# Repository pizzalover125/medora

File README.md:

# medora
A smart pill organizer. A project that saves lives.

### Why medora?
Medication nonadherence is the failure to take medication as prescribed, whether by skipping doses, taking the wrong amount, or stopping treatment early.

* Medication nonadherence contributes to roughly 125,000 deaths every year in the U.S. (Kim and Sarah A.)
* Pill organizer users saw adherence rise from 65% to as high as 100% within months (Rathod et al.)
* Patients using a smart pill organizer were 60% more compliant than those without one, nearly double the 32% improvement seen with a standard pillbox (Godin)

In the status quo, there smart pill organizers are expensive costing an average of $150 - $200 with an added monthly subscription on top. For many Americans, this is simply too out-of-reach. Additionally, many of the apps that come with the organizers are outdated and hard to use. I wanted to fix this by creating a low-cost, modern, smart pill organizer. 

### PCB

The PCB was designed in KiCAD.

### CAD

The CAD was designed in Onshape. You can view the link here: https://cad.onshape.com/documents/c1d6b76cfe1063ae9996d35d/w/b74057f0558c55e37de9882a/e/dce7fc6940c214e434cc5424?renderMode=0&uiState=6a616dc37022e90ea2108f99. There are magnets that hold together the lid and the case. 

### BOM 
A detailed bill of materials can be viewed here: https://docs.google.com/spreadsheets/d/15uKd0en9vIonSRlWCDsz52HICyDAk6iSbPfcEML8UvA/edit?usp=sharing.

### Credits
Big thanks to Hack Club for making this project possible!

### Sponsorship

This project's PCBs are sponsored by PCBWay, a leading manufacturer for PCB fabrication, assembly, 3D printing, and more.

#### About PCBWay

PCBWay offers PCB prototyping and manufacturing, PCB assembly, 3D printing, CNC machining, and other on-demand manufacturing services for makers, students, and engineers worldwide.

#### Project Background

This is a smart pill organizer — an 8-compartment device with LED indicators to help users track and remember their medication schedule. Building it required a custom PCB to house the microcontroller, LED drivers, and compartment sensors in a compact enclosure.

#### Order Process

1. **Download the Gerber files** from this repo.
2. **Go to [PCBWay.com](https://www.pcbway.com)** and click **"Instant Quote"** on the homepage.
3. **Upload the Gerber `.zip`** from this repo. PCBWay auto-detects your board dimensions, layer count, and other specs — verify these match: 190mm × 90mm, 2-layer.
4. **Set your order specs:**
   - Quantity (e.g. 5 or 10 boards)
   - Board thickness (1.6mm)
   - Copper weight (1oz standard)
   - Surface finish (HASL or ENIG)
   - Solder mask & silkscreen color
5. **Review the quote** and confirm cost/production time.
6. **Place the order** and confirm shipping address/method.
7. **Track production** — PCBWay provides status updates through fabrication and a tracking number once shipped.

#### Unboxing

Will be updated once I receive the boards!

#### Board Dimensions & Precision

Board size: 190 mm × 90 mm
Board thickness: 1.6 mm (standard)
Copper layers: 2-layer
Minimum trace width: 0.2 mm (KiCad default)
Minimum clearance: 0.2 mm (KiCad default)
Via diameter / drill: 0.6 mm / 0.3 mm (KiCad default)
Surface finish: HASL

#### End Application

The board powers the pill organizer's control system — driving LED indicators for each of the 8 compartments and interfacing with the microcontroller to track dosage timing.

#### Why PCBWay
* Fast turnaround for prototyping
* Reliable build quality at low cost for small-batch orders
* Easy Gerber upload and ordering process
* Good support for hobbyist and student projects

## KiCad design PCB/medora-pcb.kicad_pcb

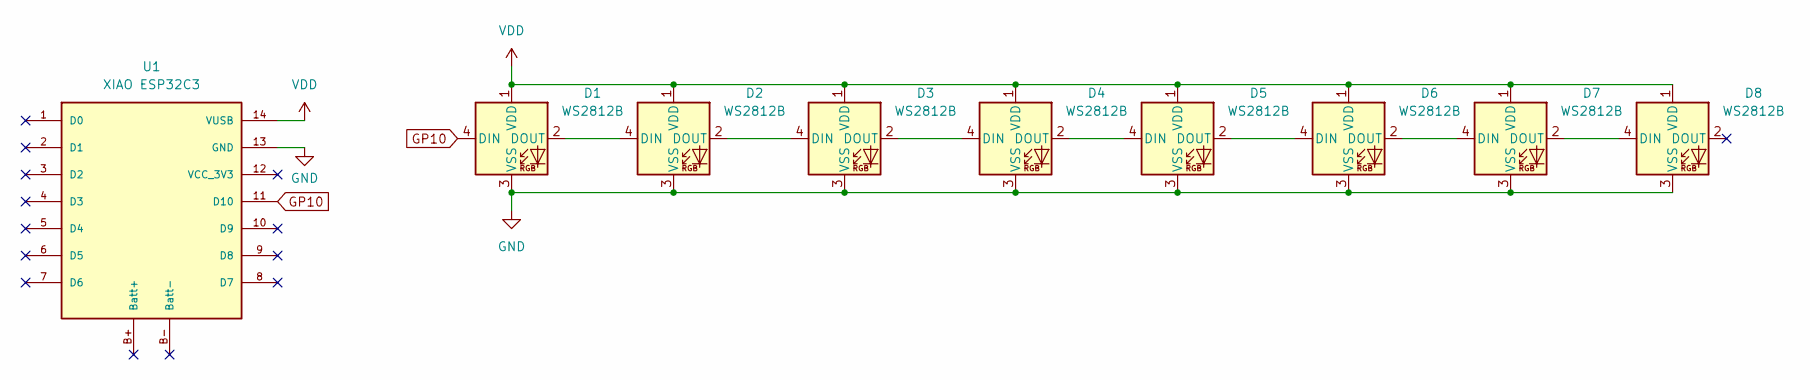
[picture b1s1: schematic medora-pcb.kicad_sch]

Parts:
D1, D2, D3, D4, D5, D6, D7, D8: WS2812B; LED_WS2812B_PLCC4_5.0x5.0mm_P3.2mm
U1: XIAO ESP32C3; xiao_esp32c3

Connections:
GND: D1.3 (VSS), D2.3 (VSS), D3.3 (VSS), D4.3 (VSS), D5.3 (VSS), D6.3 (VSS), D7.3 (VSS), D8.3 (VSS), U1.13 (GND)
GP10: D1.4 (DIN), U1.11 (D10)
unnamed: D1.2 (DOUT), D2.4 (DIN)
unnamed: D2.2 (DOUT), D3.4 (DIN)
unnamed: D3.2 (DOUT), D4.4 (DIN)
unnamed: D4.2 (DOUT), D5.4 (DIN)
unnamed: D5.2 (DOUT), D6.4 (DIN)
unnamed: D6.2 (DOUT), D7.4 (DIN)
unnamed: D7.2 (DOUT), D8.4 (DIN)
VDD: D1.1 (VDD), D2.1 (VDD), D3.1 (VDD), D4.1 (VDD), D5.1 (VDD), D6.1 (VDD), D7.1 (VDD), D8.1 (VDD), U1.14 (VUSB)

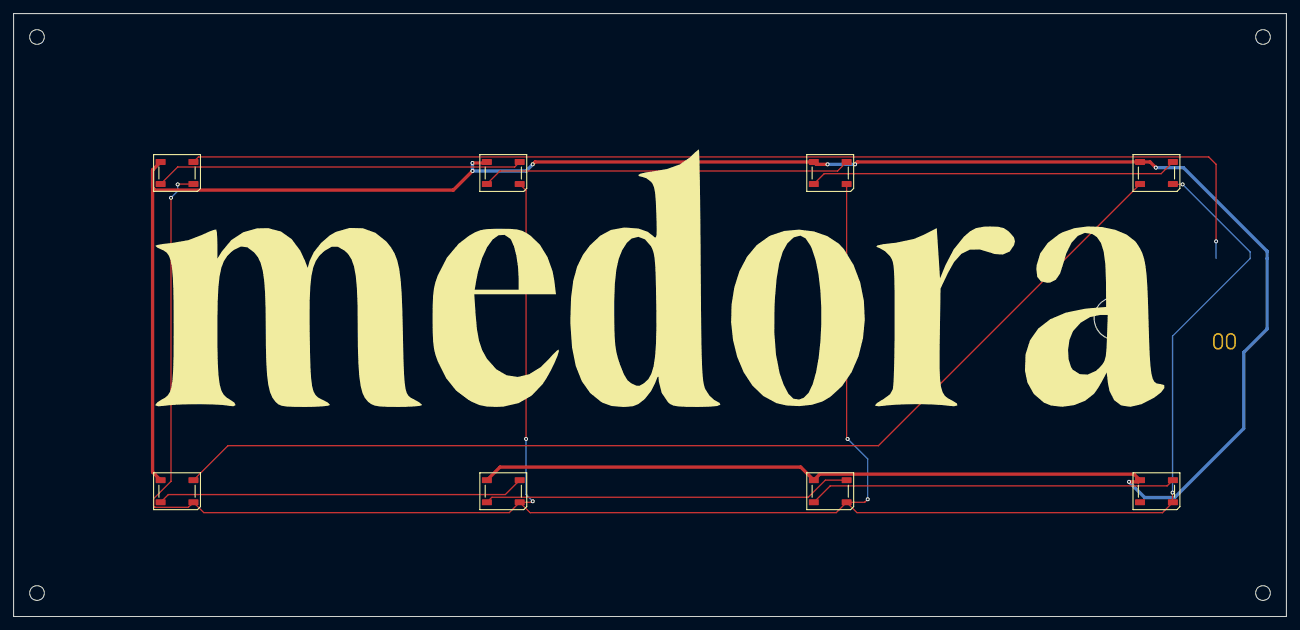
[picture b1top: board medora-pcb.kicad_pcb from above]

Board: 2 copper layers, 190.0 x 90.0 mm, 9 parts (1 on the bottom side), 10 nets.
